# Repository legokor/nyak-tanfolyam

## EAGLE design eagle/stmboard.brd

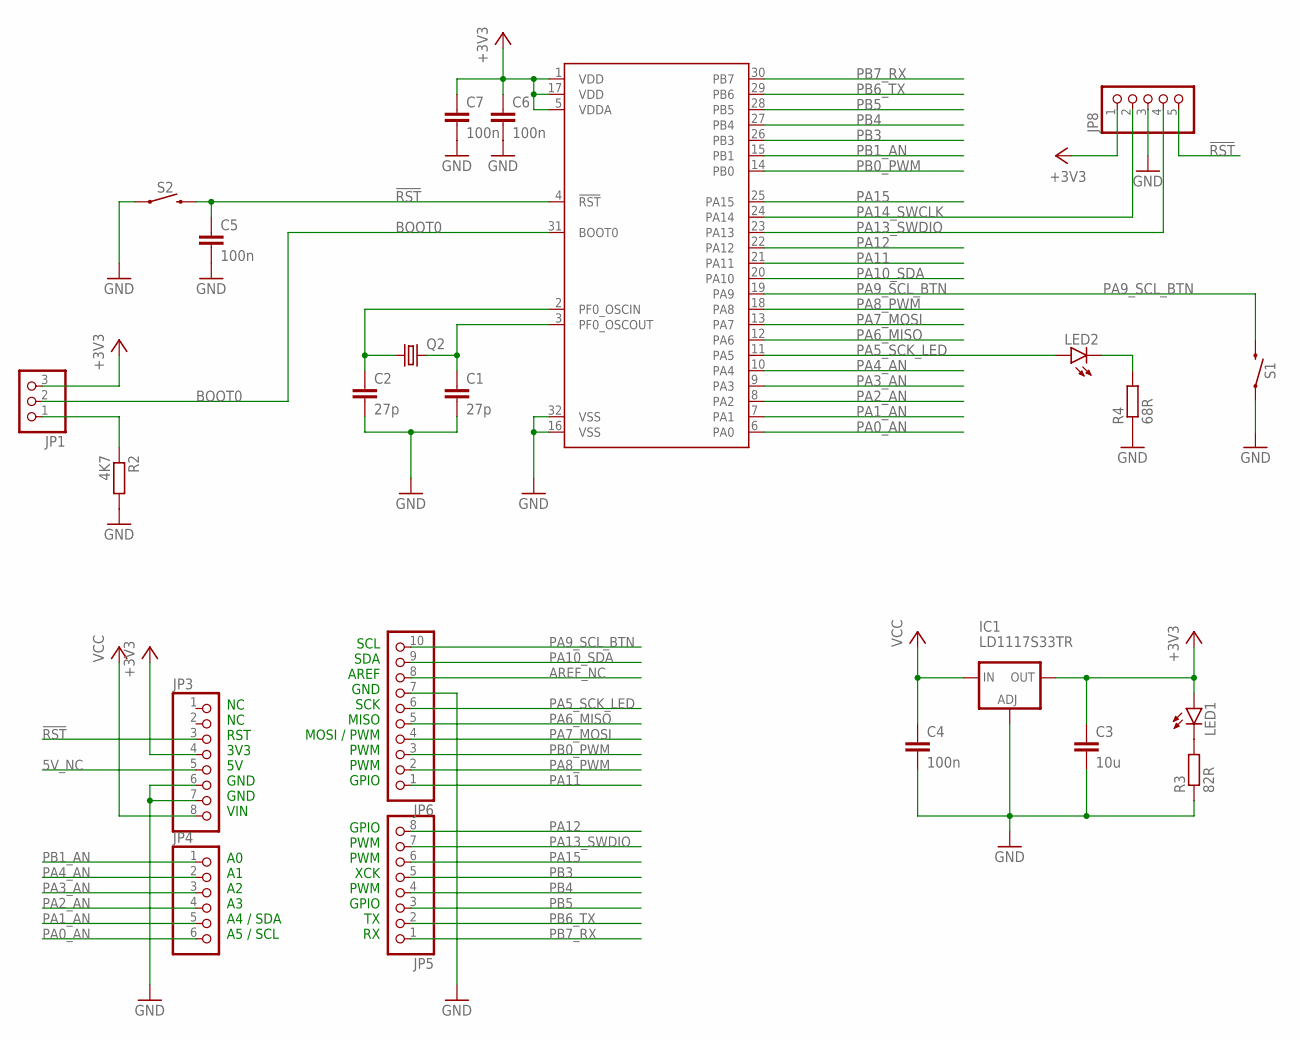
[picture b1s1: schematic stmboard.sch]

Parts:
C1, C2: 27p; C1206
C3: 10u; C1206K
C4, C5, C6, C7: 100n; C1206K
IC1: LD1117S33TR; SOT223
JP1: PINHD-1X3; 1X03
JP3, JP5: PINHD-1X8; 1X08
JP4: PINHD-1X6; 1X06
JP6: PINHD-1X10; 1X10
JP8: PINHD-1X5; 1X05
LED1, LED2: LEDSMT1206; 1206
Q2: CRYSTALSM49; SM49
R2: 4K7; M1206
R3: 82R; M1206
R4: 68R; M1206
S1, S2: MOMENTARY-SWITCH-SPST-SMD-6.0X3.5MM; TACTILE_SWITCH_SMD_6.0X3.5MM
U$1: STM32F030; TQFP32-08

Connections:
5V_NC: JP3.5
!RST: C5.1, JP3.3, JP8.5, S2.2, U$1.4 (!RST)
+3V3: C3.1, C6.1, C7.1, IC1.4 (OUT), JP1.3, JP3.4, JP8.1, LED1.A, U$1.1 (VDD), U$1.5 (VDDA), U$1.17 (VDD)
AREF_NC: JP6.8
BOOT0: JP1.2, U$1.31 (BOOT0)
GND: C1.2, C2.2, C3.2, C4.2, C5.2, C6.2, C7.2, IC1.1 (ADJ), JP3.6, JP3.7, JP6.7, JP8.3, R2.2, R3.1, R4.1, S1.1, S2.1, U$1.16 (VSS), U$1.32 (VSS)
unnamed: LED1.C, R3.2
unnamed: LED2.C, R4.2
unnamed: JP1.1, R2.1
OSCI: C2.1, Q2.1, U$1.2 (PF0_OSCIN)
OSCO: C1.1, Q2.2, U$1.3 (PF0_OSCOUT)
PA0_AN: JP4.6, U$1.6 (PA0)
PA1_AN: JP4.5, U$1.7 (PA1)
PA2_AN: JP4.4, U$1.8 (PA2)
PA3_AN: JP4.3, U$1.9 (PA3)
PA4_AN: JP4.2, U$1.10 (PA4)
PA5_SCK_LED: JP6.6, LED2.A, U$1.11 (PA5)
PA6_MISO: JP6.5, U$1.12 (PA6)
PA7_MOSI: JP6.4, U$1.13 (PA7)
PA8_PWM: JP6.2, U$1.18 (PA8)
PA9_SCL_BTN: JP6.10, S1.2, U$1.19 (PA9)
PA10_SDA: JP6.9, U$1.20 (PA10)
PA11: JP6.1, U$1.21 (PA11)
PA12: JP5.8, U$1.22 (PA12)
PA13_SWDIO: JP5.7, JP8.4, U$1.23 (PA13)
PA14_SWCLK: JP8.2, U$1.24 (PA14)
PA15: JP5.6, U$1.25 (PA15)
PB0_PWM: JP6.3, U$1.14 (PB0)
PB1_AN: JP4.1, U$1.15 (PB1)
PB3: JP5.5, U$1.26 (PB3)
PB4: JP5.4, U$1.27 (PB4)
PB5: JP5.3, U$1.28 (PB5)
PB6_TX: JP5.2, U$1.29 (PB6)
PB7_RX: JP5.1, U$1.30 (PB7)
VCC: C4.1, IC1.3 (IN), JP3.8

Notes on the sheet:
NC NC RST 3V3 5V GND GND VIN
A0 A1 A2 A3 A4 / SDA A5 / SCL
SCL SDA AREF GND SCK MISO MOSI / PWM PWM PWM GPIO
GPIO PWM PWM XCK PWM GPIO TX RX

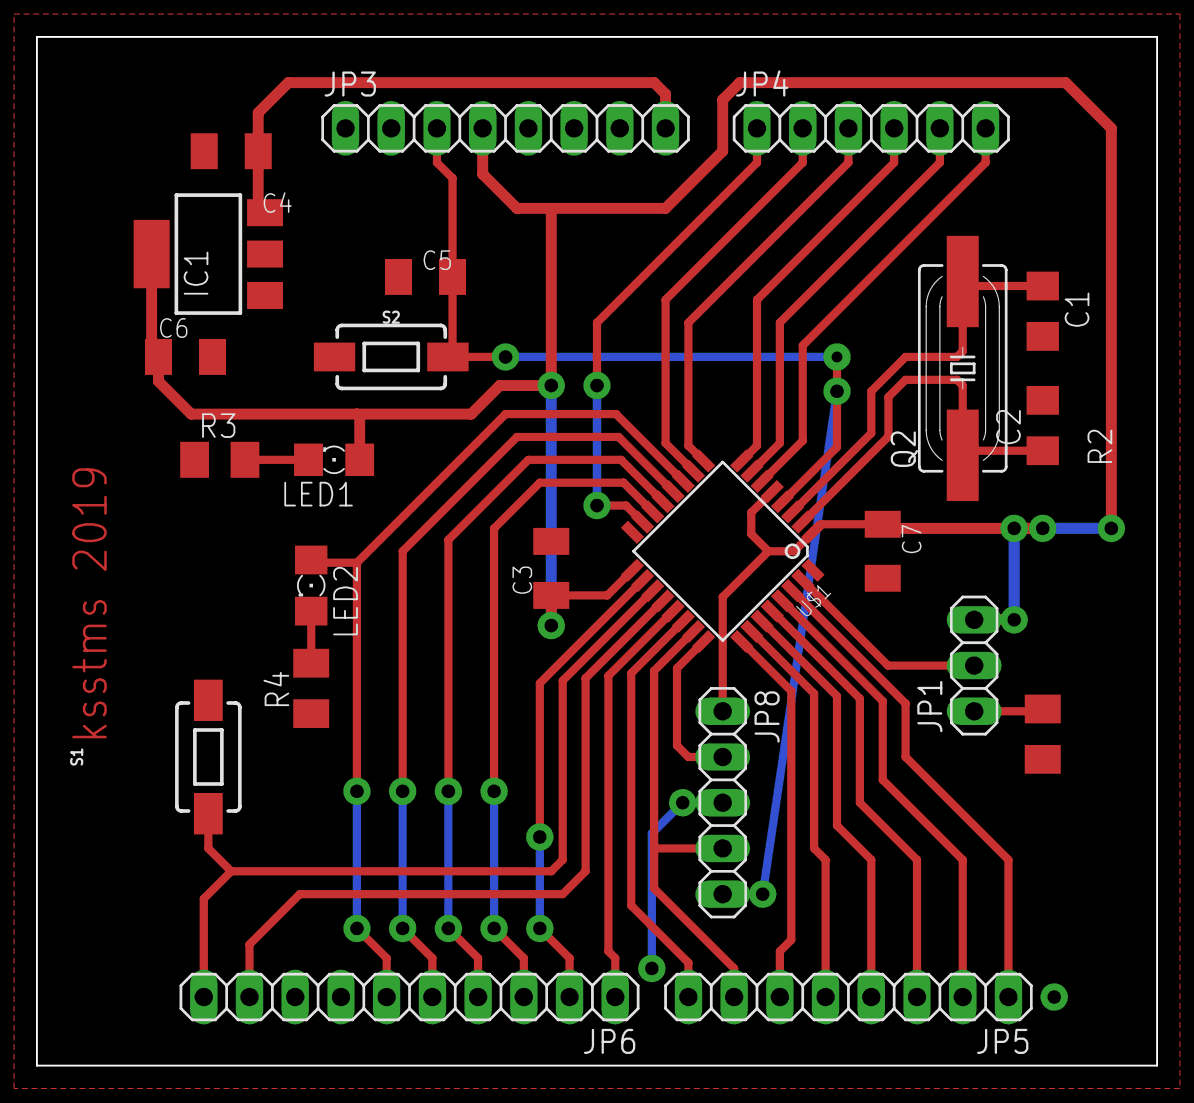
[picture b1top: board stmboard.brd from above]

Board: 2 copper layers, 62.2 x 57.1 mm, 23 parts (0 on the bottom side), 33 nets.

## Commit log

2019-04-22 initial version
2019-04-22 updated eagle version
2019-04-22 fixed arduino header spacing
2019-04-22 changed boot0 jumper to 3-pin
2019-04-22 added gitignore
2019-04-22 made via diameters bigger
2019-04-22 some wiring touch-ups
2019-04-23 more wiring touch-ups
2019-04-23 added part values
2019-04-23 fixed SWDIO/SWCLK signal names
2019-04-23 fixed value labels on brd
2019-05-15 added simple example project

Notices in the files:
parts and their libraries:
SparkFun-Switches: Licensing: Creative Commons ShareAlike 4.0 International - https://creativecommons.org/licenses/by-sa/4.0
